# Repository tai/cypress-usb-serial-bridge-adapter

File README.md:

# cypress-usb-serial-bridge-adapter
KiCad design file for Cypress USB-Serial Bridge Adapter

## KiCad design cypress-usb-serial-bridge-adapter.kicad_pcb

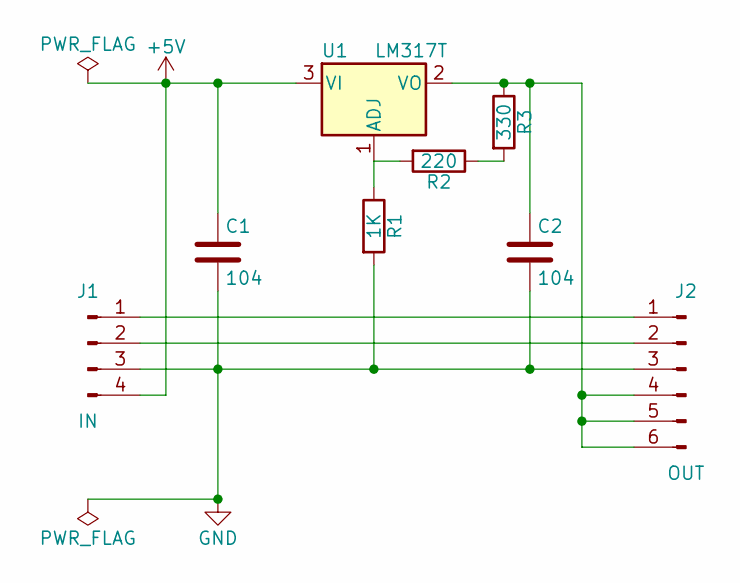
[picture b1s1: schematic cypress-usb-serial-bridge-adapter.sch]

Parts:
C1, C2: 104; C_Disc_D3.8mm_W2.6mm_P2.50mm
J1: IN; Pin_Header_Straight_1x04_Pitch2.54mm
J2: OUT; Pin_Header_Straight_1x06_Pitch2.54mm
R1: 1K; R_Axial_DIN0204_L3.6mm_D1.6mm_P2.54mm_Vertical
R2: 220; R_Axial_DIN0204_L3.6mm_D1.6mm_P2.54mm_Vertical
R3: 330; R_Axial_DIN0204_L3.6mm_D1.6mm_P2.54mm_Vertical
U1: LM317T; TO-220

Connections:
+5V: C1.1, J1.4, U1.3 (VI)
GND: C1.2, C2.2, J1.3, J2.3, R1.2
unnamed: C2.1, J2.4, J2.5, J2.6, R3.1, U1.2 (VO)
unnamed: J1.1, J2.1
unnamed: J1.2, J2.2
unnamed: R1.1, R2.2, U1.1 (ADJ)
unnamed: R2.1, R3.2

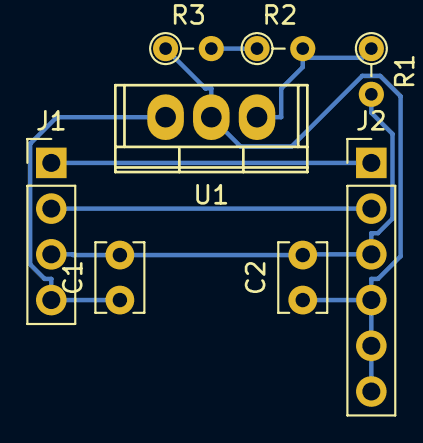
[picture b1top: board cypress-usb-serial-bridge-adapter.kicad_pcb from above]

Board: 2 copper layers, 8 parts (0 on the bottom side), 7 nets.
